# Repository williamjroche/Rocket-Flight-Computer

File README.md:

# Zeus Flight Computer

Custom flight computer for amature rockets, code named Zeus. This FC records flight data, detects apogee using a 9-axis IMU + baraomter sensor, has a built in pyro circut for firing e-matches (parachute, stage seperation, etc.).

## Project Status

- PCB design in the works, based on my Atlas Flight Controller from this project: https://github.com/williamjroche/Autonomous_drone
- Prototyping in progress on protoboard
- Board not yet fabricated, working on completing prototype first to test architecture

## Features

- 3 pyro channels with continuity sensing
- IMU + barometer sensors for apogee detection
- microSD card reader for data logging
- Automatic USB / external battery power switching (using PMOS switching circuit)
- MicroPython firmware (adapted from drone flight controller project)

## Hardware Overview

- Check out my system diagrams: [System Drawings](./System%20Drawings)
    - Explains architecture at a top level overview
- Key components table (MCU, IMU, barometer, flash, SD, pyro MOSFETs, power management)
- Link to schematic/PCB files [Zeus_FC_PCB](./Zeus_FC_PCB)

## PCB

- Stackup summary (4-layer: signal / GND / 3.3V / signal)
- Check out other photos [PCB Photos](./PCB%20Photos)
- Note: working on finding smaller SMD type IRFZ44N mosfets because these are ugly

## Protoboard Prototype

- Purpose: validate firmware and circuit behavior ahead of PCB fabrication
- Hardware used (Pico 2W, IMU breakout (ICM-20948), barometer breakout (BPM 384), microSD breakout, custom designed and fabricated 12v to 3.3v regulator board)
- Photos coming soon

## Firmware

- project specific firmware not yet developed, coming soon
- Firmware will be based off of Atlas FC firmware: https://github.com/williamjroche/Autonomous_drone/tree/main/flight_controller

## Wiring / Pinout

- Micro SD card reader:
  - CS – GPIO8
  - MISO – GPIO16
  - SCK – GPIO18
  - MOSI – GPIO19
- IMU Board:
  - SDA – GPIO0
  - SCL – GPIO1
- Barometer:
  - SDA: GPIO20
  - SCL: GPIO21

## Getting Started / Prototype Setup

If you want to make your own prototype, you'll need the following materials:

- protoboard, decently sized (mine is 7cm x 9cm)
- soldering iron
- solder (I recommend lead free)
- Fume extractor
- something to clean the soldering iron tip, like steel wool)
- 22awg wire
- Toggle switches (2)
- 1 3s LiPO battery
- Something to convert the 11.1v LiPO battery to 3.3v for the Pi
    - A buck converter off amazon will work
    - or you can download the files from the device I built from here: (https://github.com/williamjroche/Autonomous_drone/tree/main/dual_power_supply)
        - Can be fabricated using PCBway, JLCPCB, or any of your favorite fabricators. I ordered from PCBway.
- Raspberry Pi Pico 2W
- ICM-20948 IMU breakout
- BPM 384 barometer breakout
- Any microSD card reader breakout
- Electrical tape or hot glue
- MicroSD card
- Flux to make soldering easier
- Multimeter to test electrical connections (not needed but helpful)

## My Prototype: 

Here is a demo video of the working prototype: https://youtube.com/shorts/D4aav9IAWUg?si=ib71gM45oc4MuGbN

At the moment only the IMU is programmed, I need to work on the barometer sensor and apogee detection + saving data to micro SD card. You can see in the video I am using my custom dual power PCB I designed which is converting the 12v from the battery to a usable 3.3v for our sensors and Pico 2W. The switch you see is me prototyping a power switch.

## Safety Notes

- Be careful handling pyro charges!
      - I am not responible for any accidents.

## Acknowledgments

- Link to drone flight controller project: https://github.com/williamjroche/Autonomous_drone/tree/main
    - Dual Power Supply PCB is the 12v to 3.3v converter I am using on this project. The explaination under this other repo readme will help clear up any   confusion.

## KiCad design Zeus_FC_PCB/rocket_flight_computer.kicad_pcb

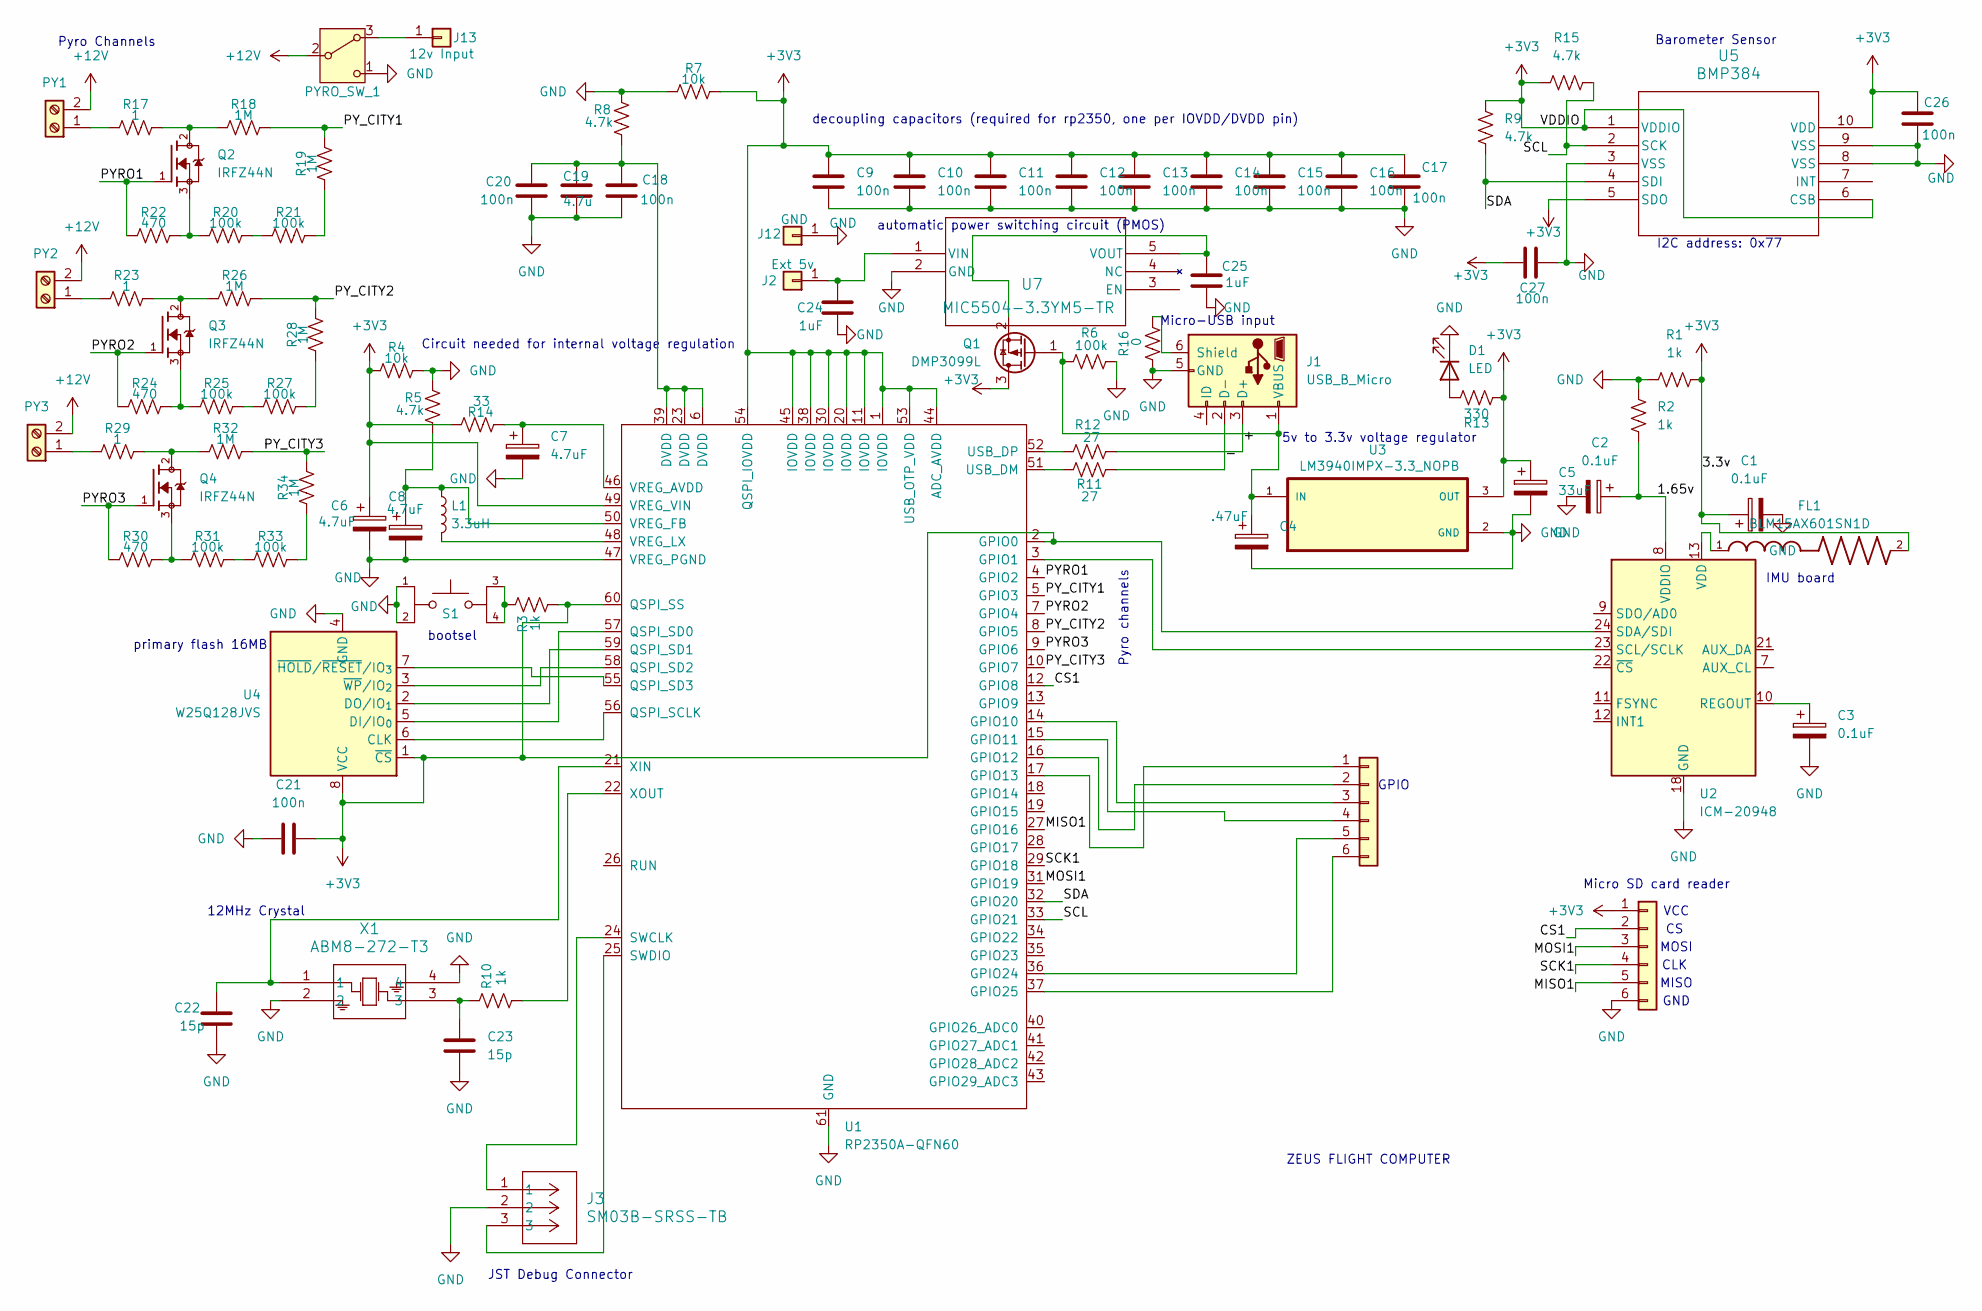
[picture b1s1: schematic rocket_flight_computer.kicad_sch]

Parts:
C1, C2, C3: 0.1uF; C_0402_1005Metric
C4: .47uF; C_0402_1005Metric
C5: 33uF; C_0402_1005Metric
C6, C7, C8: 4.7uF; C_0402_1005Metric
C9, C10, C11, C12, C13, C14, C15, C16, C17, C18, C20, C21, C26, C27: 100n; C_0402_1005Metric
C19: 4.7u; C_0402_1005Metric
C22, C23: 15p; C_0402_1005Metric
C24, C25: 1uF; C_0402_1005Metric
D1: LED; LED_CMD15-21_VCC
FL1: BLM15AX601SN1D; BEADC1005X55N; DigiKey_Part_Number 490-5441-1-ND
J1: USB_B_Micro; AMPHENOL_10118192-0001LF
J2: Ext 5v; SolderWirePad_1x01_SMD_2x4mm
J3: SM03B-SRSS-TB; CONN_SM03B-SRSS-TB_JST
J4, J6: Conn_01x06; PinHeader_1x06_P2.54mm_Vertical
J12: GND; SolderWirePad_1x01_SMD_2x4mm
J13: 12v Input; SolderWirePad_1x01_SMD_2x4mm
L1: 3.3uH; L_Cenker_CKCS201610
PY1, PY2, PY3: Screw_Terminal_01x02; 691137710002
PYRO_SW_1: SW_Nidec_CAS-120A1; SW_100SP1T1B4M2QE
Q1: DMP3099L; SOT-23
Q2, Q3, Q4: IRFZ44N; TO254P1016X419X2286-3; PARTREV 09/21/10
R1, R2, R3, R10: 1k; R_0402_1005Metric
R4, R7: 10k; R_0402_1005Metric
R5, R8, R9, R15: 4.7k; R_0402_1005Metric
R6, R20, R21, R25, R27, R31, R33: 100k; R_0402_1005Metric
R11, R12: 27; R_0402_1005Metric
R13: 330; R_0402_1005Metric
R14: 33; R_0402_1005Metric
R16: 0; R_0402_1005Metric
R17, R23, R29: 1; R_0402_1005Metric
R18, R19, R26, R28, R32, R34: 1M; R_0402_1005Metric
R22, R24, R30: 470; R_0402_1005Metric
S1: TL3365AF180QG; SW_TL3365AF180QG; PARTREV A; DigiKey_Part_Number EG5384CT-ND
U1: RP2350A-QFN60; RP2350A_QFN-60_EP_7.75x7.75_Pitch0.4mm
U2: ICM-20948; QFN40P300X300X105-24N
U3: LM3940IMPX-3.3_NOPB; SOT230P700X180-4N; DigiKey_Part_Number LM3940IMPX-3.3/NOPBCT-ND
U4: W25Q128JVS; SOIC-8_5.3x5.3mm_P1.27mm
U5: BMP384; LGA10_2.0X2.0X0.95_BOS
U7: MIC5504-3.3YM5-TR; SOT-23-5_MC_MCH
X1: ABM8-272-T3; ABM8-272-T3_ABR

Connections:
+3V3: C1.1, C5.1, C6.1, C9.1, C10.1, C11.1, C12.1, C13.1, C14.1, C15.1, C16.1, C17.1, C21.1, C26.1, C27.1, FL1.2, J4.1, Q1.3 (D), R1.2, R3.1, R4.2, R7.1, R9.2, R13.2, R14.1, R15.2, U1.1 (IOVDD), U1.2 (GPIO0), U1.11 (IOVDD), U1.20 (IOVDD), U1.30 (IOVDD), U1.38 (IOVDD), U1.44 (ADC_AVDD), U1.45 (IOVDD), U1.49 (VREG_VIN), U1.53 (USB_OTP_VDD), U1.54 (QSPI_IOVDD), U1.60 (QSPI_SS), U2.24 (SDA/SDI), U3.3 (OUT), U4.1 (~CS), U4.8 (VCC), U5.1 (VDDIO), U5.5 (SDO), U5.6 (CSB), U5.10 (VDD)
+12V: PY1.2, PY2.2, PY3.2, PYRO_SW_1.2 (B)
/1.65v: C2.1, R2.1, U2.8 (VDDIO)
/+: J1.3 (D+), R12.2
/-: J1.2 (D-), R11.2
/CS1: J4.2, U1.12 (GPIO8)
/MISO1: J4.5, U1.27 (GPIO16)
/MOSI1: J4.3, U1.31 (GPIO19)
/PYRO1: Q2.1, R22.2, U1.4 (GPIO2)
/PYRO2: Q3.1, R24.2, U1.7 (GPIO4)
/PYRO3: Q4.1, R30.2, U1.9 (GPIO6)
/PY_CITY1: R18.1, R19.1, U1.5 (GPIO3)
/PY_CITY2: R26.1, R28.1, U1.8 (GPIO5)
/PY_CITY3: R32.1, R34.1, U1.10 (GPIO7)
/SCK1: J4.4, U1.29 (GPIO18)
/SCL: R15.1, U1.33 (GPIO21), U5.2 (SCK)
/SDA: R9.1, U1.32 (GPIO20), U5.4 (SDI)
GND: C1.2, C2.2, C3.2, C4.2, C5.2, C6.2, C7.2, C8.2, C9.2, C10.2, C11.2, C12.2, C13.2, C14.2, C15.2, C16.2, C17.2, C18.2, C19.2, C20.2, C21.2, C22.2, C23.2, C24.2, C25.2, C26.2, C27.2, D1.1 (K), J1.5 (GND), J3.2, J4.6, J12.1, PYRO_SW_1.1 (C), R1.1, R2.2, R4.1, R5.2, R6.2, R7.2, R8.2, R16.1, S1.1, S1.2, U1.47 (VREG_PGND), U1.61 (GND), U2.18 (GND), U2.20 (GND), U3.2 (GND), U3.4 (GND), U4.4 (GND), U5.3 (VSS), U5.8 (VSS), U5.9 (VSS), U7.2 (GND), X1.2, X1.4
unnamed: C18.1, C19.1, C20.1, R8.1, U1.6 (DVDD), U1.23 (DVDD), U1.39 (DVDD)
unnamed: C23.1, R10.2, X1.3
unnamed: D1.2 (A), R13.1
unnamed: J1.6 (Shield), R16.2
unnamed: C4.1, J1.1 (VBUS), Q1.1 (G), R6.1, U3.1 (IN)
unnamed: C24.1, J2.1, U7.1 (VIN)
unnamed: J6.1, U1.17 (GPIO13)
unnamed: J6.2, U1.16 (GPIO12)
unnamed: J6.3, U1.14 (GPIO10)
unnamed: J6.4, U1.15 (GPIO11)
unnamed: J6.5, U1.36 (GPIO24)
unnamed: J6.6, U1.37 (GPIO25)
unnamed: J13.1, PYRO_SW_1.3 (A)
unnamed: PY1.1, R17.2
unnamed: PY2.1, R23.2
unnamed: PY3.1, R29.2
unnamed: C25.1, Q1.2 (S), U7.5 (VOUT)
unnamed: Q2.2, R17.1, R18.2
unnamed: Q2.3, R20.2, R22.1
unnamed: Q3.2, R23.1, R26.2
unnamed: Q3.3, R24.1, R25.2
unnamed: Q4.2, R29.1, R32.2
unnamed: Q4.3, R30.1, R31.2
unnamed: R3.2, S1.3, S1.4
unnamed: R19.2, R21.1
unnamed: R20.1, R21.2
unnamed: R25.1, R27.2
unnamed: R27.1, R28.2
unnamed: R31.1, R33.2
unnamed: R33.1, R34.2
unnamed: U1.3 (GPIO1), U2.23 (SCL/SCLK)
unnamed: U1.56 (QSPI_SCLK), U4.6 (CLK)
unnamed: U1.57 (QSPI_SD0), U4.5 (DI/IO_{0})
unnamed: U1.59 (QSPI_SD1), U4.2 (DO/IO_{1})
unnamed: U1.58 (QSPI_SD2), U4.3 (~WP/IO_{2})
unnamed: U1.55 (QSPI_SD3), U4.7 (~HOLD/~RESET/IO_{3})
unnamed: J3.1, U1.24 (SWCLK)
unnamed: J3.3, U1.25 (SWDIO)
unnamed: R11.1, U1.51 (USB_DM)
unnamed: R12.1, U1.52 (USB_DP)
unnamed: C7.1, R14.2, U1.46 (VREG_AVDD)
unnamed: C8.1, L1.1, R5.1, U1.50 (VREG_FB)
unnamed: L1.2, U1.48 (VREG_LX)
unnamed: C22.1, U1.21 (XIN), X1.1
unnamed: R10.1, U1.22 (XOUT)
unnamed: C3.1, U2.10 (REGOUT)
unnamed: FL1.1, U2.13 (VDD)

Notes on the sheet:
5v to 3.3v voltage regulator
GND
I2C address: 0x77
JST Debug Connector
Barometer Sensor
primary flash 16MB
12MHz Crystal
automatic power switching circuit (PMOS)
CLK
Micro-USB input
IMU board
Pyro Channels
MISO
decoupling capacitors (required for rp2350, one per IOVDD/DVDD pin)
Circuit needed for internal voltage regulation
VCC
bootsel
GPIO
ZEUS FLIGHT COMPUTER
MOSI
Pyro channels
Micro SD card reader

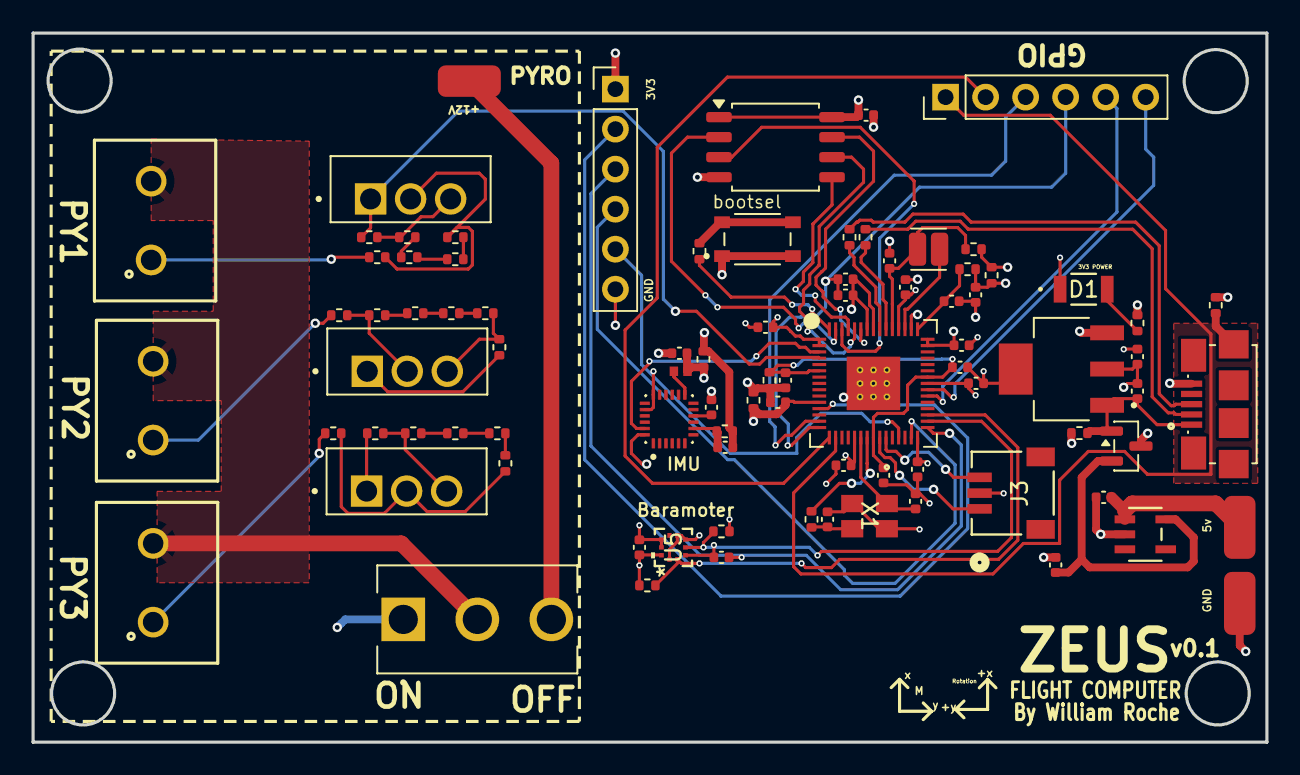
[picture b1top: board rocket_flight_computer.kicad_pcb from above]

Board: 4 copper layers, 78.3 x 45.0 mm, 87 parts (0 on the bottom side), 64 nets.
